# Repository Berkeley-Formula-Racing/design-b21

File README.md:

View this project on [CADLAB.io](https://cadlab.io/project/23941). 

# BFR Electrical Design - B21

## VCS
[CadLab Repo](https://cadlab.io/berkeley-formula-racing)

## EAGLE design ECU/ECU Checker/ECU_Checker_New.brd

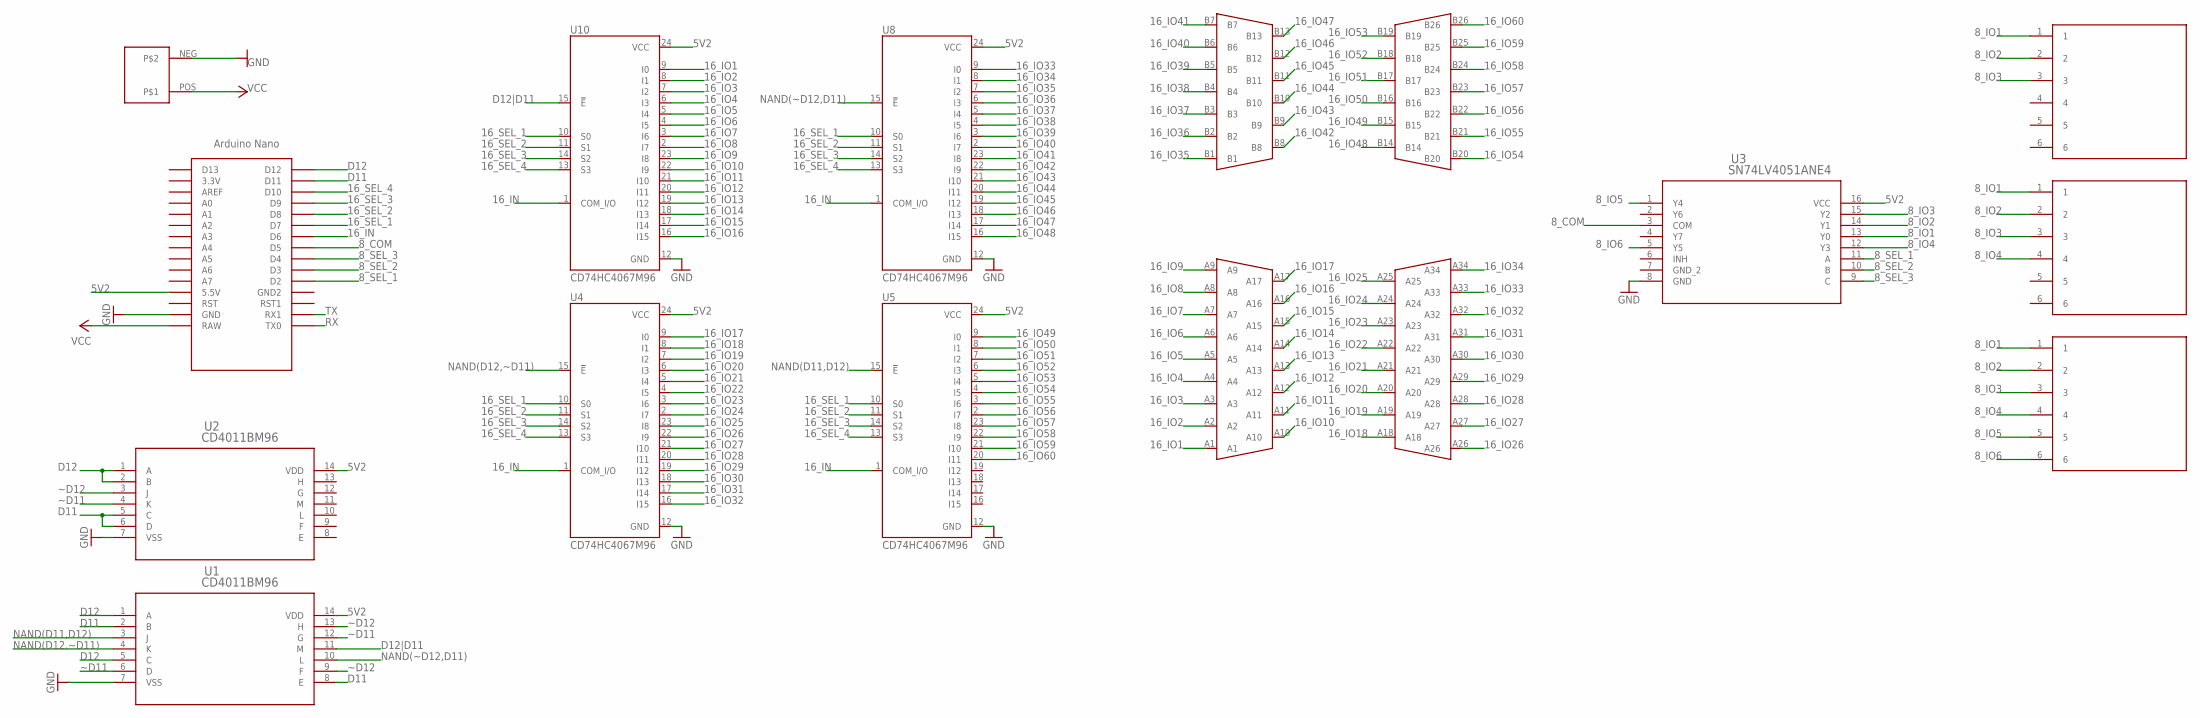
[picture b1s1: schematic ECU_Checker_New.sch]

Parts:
U1, U2: CD4011BM96; D14
U3: SN74LV4051ANE4; N16
U4, U5, U8, U10: CD74HC4067M96; SOIC127P1030X265-24N
U$2: NANO
U$3, U$5, U$6: DTM_CON; DTM_CON_F
U$4: BATTERY; BATTERY_F
U$7: MOTEC_400_CON; MOTEC_400_CON_F

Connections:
5V2: U1.14 (VDD), U2.14 (VDD), U3.16 (VCC), U4.24 (VCC), U5.24 (VCC), U8.24 (VCC), U10.24 (VCC), U$2.5V (5.5V)
8_COM: U3.3 (COM), U$2.D5
8_IO1: U3.13 (Y0), U$3.1, U$5.1, U$6.1
8_IO2: U3.14 (Y1), U$3.2, U$5.2, U$6.2
8_IO3: U3.15 (Y2), U$3.3, U$5.3, U$6.3
8_IO4: U3.12 (Y3), U$5.4, U$6.4
8_IO5: U3.1 (Y4), U$6.5
8_IO6: U3.5 (Y5), U$6.6
8_SEL_1: U3.11 (A), U$2.D2
8_SEL_2: U3.10 (B), U$2.D3
8_SEL_3: U3.9 (C), U$2.D4
16_IN: U4.1 (COM_I/O), U5.1 (COM_I/O), U8.1 (COM_I/O), U10.1 (COM_I/O), U$2.D6
16_IO1: U10.9 (I0), U$7.A1
16_IO2: U10.8 (I1), U$7.A2
16_IO3: U10.7 (I2), U$7.A3
16_IO4: U10.6 (I3), U$7.A4
16_IO5: U10.5 (I4), U$7.A5
16_IO6: U10.4 (I5), U$7.A6
16_IO7: U10.3 (I6), U$7.A7
16_IO8: U10.2 (I7), U$7.A8
16_IO9: U10.23 (I8), U$7.A9
16_IO10: U10.22 (I9), U$7.A10
16_IO11: U10.21 (I10), U$7.A11
16_IO12: U10.20 (I11), U$7.A12
16_IO13: U10.19 (I12), U$7.A13
16_IO14: U10.18 (I13), U$7.A14
16_IO15: U10.17 (I14), U$7.A15
16_IO16: U10.16 (I15), U$7.A16
16_IO17: U4.9 (I0), U$7.A17
16_IO18: U4.8 (I1), U$7.A18
16_IO19: U4.7 (I2), U$7.A19
16_IO20: U4.6 (I3), U$7.A20
16_IO21: U4.5 (I4), U$7.A21
16_IO22: U4.4 (I5), U$7.A22
16_IO23: U4.3 (I6), U$7.A23
16_IO24: U4.2 (I7), U$7.A24
16_IO25: U4.23 (I8), U$7.A25
16_IO26: U4.22 (I9), U$7.A26
16_IO27: U4.21 (I10), U$7.A27
16_IO28: U4.20 (I11), U$7.A28
16_IO29: U4.19 (I12), U$7.A29
16_IO30: U4.18 (I13), U$7.A30
16_IO31: U4.17 (I14), U$7.A31
16_IO32: U4.16 (I15), U$7.A32
16_IO33: U8.9 (I0), U$7.A33
16_IO34: U8.8 (I1), U$7.A34
16_IO35: U8.7 (I2), U$7.B1
16_IO36: U8.6 (I3), U$7.B2
16_IO37: U8.5 (I4), U$7.B3
16_IO38: U8.4 (I5), U$7.B4
16_IO39: U8.3 (I6), U$7.B5
16_IO40: U8.2 (I7), U$7.B6
16_IO41: U8.23 (I8), U$7.B7
16_IO42: U8.22 (I9), U$7.B8
16_IO43: U8.21 (I10), U$7.B9
16_IO44: U8.20 (I11), U$7.B10
16_IO45: U8.19 (I12), U$7.B11
16_IO46: U8.18 (I13), U$7.B12
16_IO47: U8.17 (I14), U$7.B13
16_IO48: U8.16 (I15), U$7.B14
16_IO49: U5.9 (I0), U$7.B15
16_IO50: U5.8 (I1), U$7.B16
16_IO51: U5.7 (I2), U$7.B17
16_IO52: U5.6 (I3), U$7.B18
16_IO53: U5.5 (I4), U$7.B19
16_IO54: U5.4 (I5), U$7.B20
16_IO55: U5.3 (I6), U$7.B21
16_IO56: U5.2 (I7), U$7.B22
16_IO57: U5.23 (I8), U$7.B23
16_IO58: U5.22 (I9), U$7.B24
16_IO59: U5.21 (I10), U$7.B25
16_IO60: U5.20 (I11), U$7.B26
16_SEL_1: U4.10 (S0), U5.10 (S0), U8.10 (S0), U10.10 (S0), U$2.D7
16_SEL_2: U4.11 (S1), U5.11 (S1), U8.11 (S1), U10.11 (S1), U$2.D8
16_SEL_3: U4.14 (S2), U5.14 (S2), U8.14 (S2), U10.14 (S2), U$2.D9
16_SEL_4: U4.13 (S3), U5.13 (S3), U8.13 (S3), U10.13 (S3), U$2.D10
D11: U1.2 (B), U1.8 (E), U2.5 (C), U2.6 (D), U$2.D11
D12: U1.1 (A), U1.5 (C), U2.1 (A), U2.2 (B), U$2.D12
D12|D11: U1.11 (M), U10.15 (!E)
GND: U1.7 (VSS), U2.7 (VSS), U3.8 (GND), U4.12 (GND), U5.12 (GND), U8.12 (GND), U10.12 (GND), U$2.GND, U$4.NEG
GND_2: U3.7 (GND_2)
NAND(D11,D12): U1.3 (J), U5.15 (!E)
NAND(D12,~D11): U1.4 (K), U4.15 (!E)
NAND(~D12,D11): U1.10 (L), U8.15 (!E)
RX: U$2.TX0
TX: U$2.RX1
VCC: U$2.RAW, U$4.POS
~D11: U1.6 (D), U1.12 (G), U2.4 (K)
~D12: U1.9 (F), U1.13 (H), U2.3 (J)

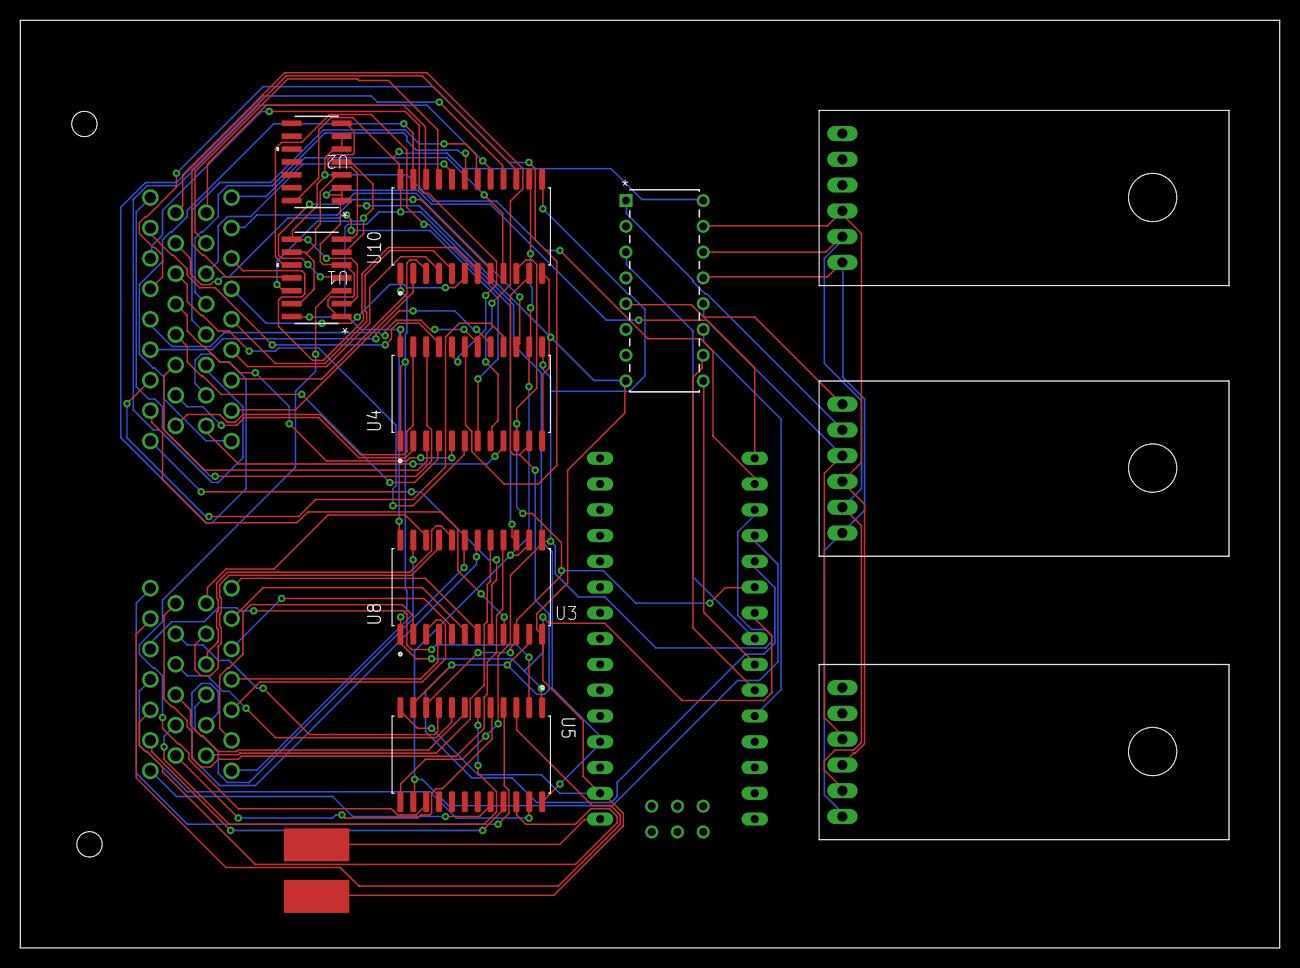
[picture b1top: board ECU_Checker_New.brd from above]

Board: 2 copper layers, 124.1 x 91.4 mm, 13 parts (0 on the bottom side), 86 nets.

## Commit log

2020-10-24 Dirs
2020-10-24 gitignore
2020-10-24 Add ecu checker board
2021-02-20 Add abstract connection, testing
2021-02-28 Backlink to CADLAB.io has been added.
2021-04-15 added BPSD.sch
2021-04-22 Add Accel board
2021-04-22 Added BPD/BPD.sch
2021-04-22 Remove /bpd
2021-04-22 Added BPD/BPD.pro
